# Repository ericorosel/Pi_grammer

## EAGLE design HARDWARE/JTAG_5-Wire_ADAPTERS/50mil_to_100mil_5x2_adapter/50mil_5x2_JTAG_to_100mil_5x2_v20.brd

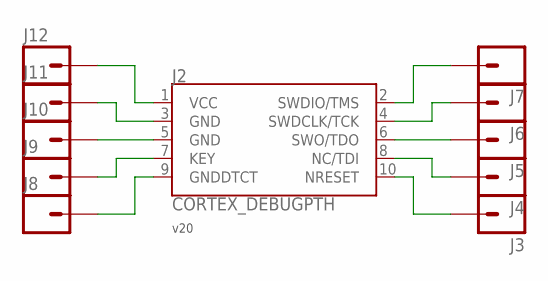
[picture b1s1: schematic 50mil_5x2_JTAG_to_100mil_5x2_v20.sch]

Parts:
J2: CORTEX_DEBUGPTH; 2X5-PTH-1.27MM
J3, J4, J5, J6, J7, J8, J9, J10, J11, J12: M01OFFSET; 1X01_OFFSET

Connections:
unnamed: J2.10 (NRESET), J3.1
unnamed: J2.8 (NC/TDI), J4.1
unnamed: J2.6 (SWO/TDO), J5.1
unnamed: J2.4 (SWDCLK/TCK), J6.1
unnamed: J2.2 (SWDIO/TMS), J7.1
unnamed: J2.1 (VCC), J12.1
unnamed: J2.3 (GND), J11.1
unnamed: J2.5 (GND), J10.1
unnamed: J2.7 (KEY), J9.1
unnamed: J2.9 (GNDDTCT), J8.1

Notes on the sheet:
v20

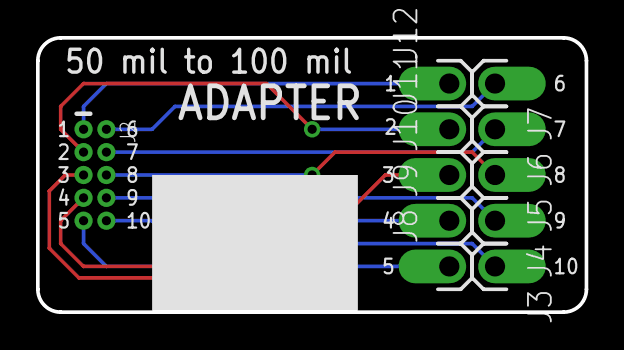
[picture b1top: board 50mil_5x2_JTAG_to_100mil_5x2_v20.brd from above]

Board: 2 copper layers, 30.5 x 15.2 mm, 11 parts (0 on the bottom side), 10 nets.

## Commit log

2018-01-08 restructured folders in repo

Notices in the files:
parts and their libraries:
SparkFun-Connectors: Licensing: Creative Commons ShareAlike 4.0 International - https://creativecommons.org/licenses/by-sa/4.0
